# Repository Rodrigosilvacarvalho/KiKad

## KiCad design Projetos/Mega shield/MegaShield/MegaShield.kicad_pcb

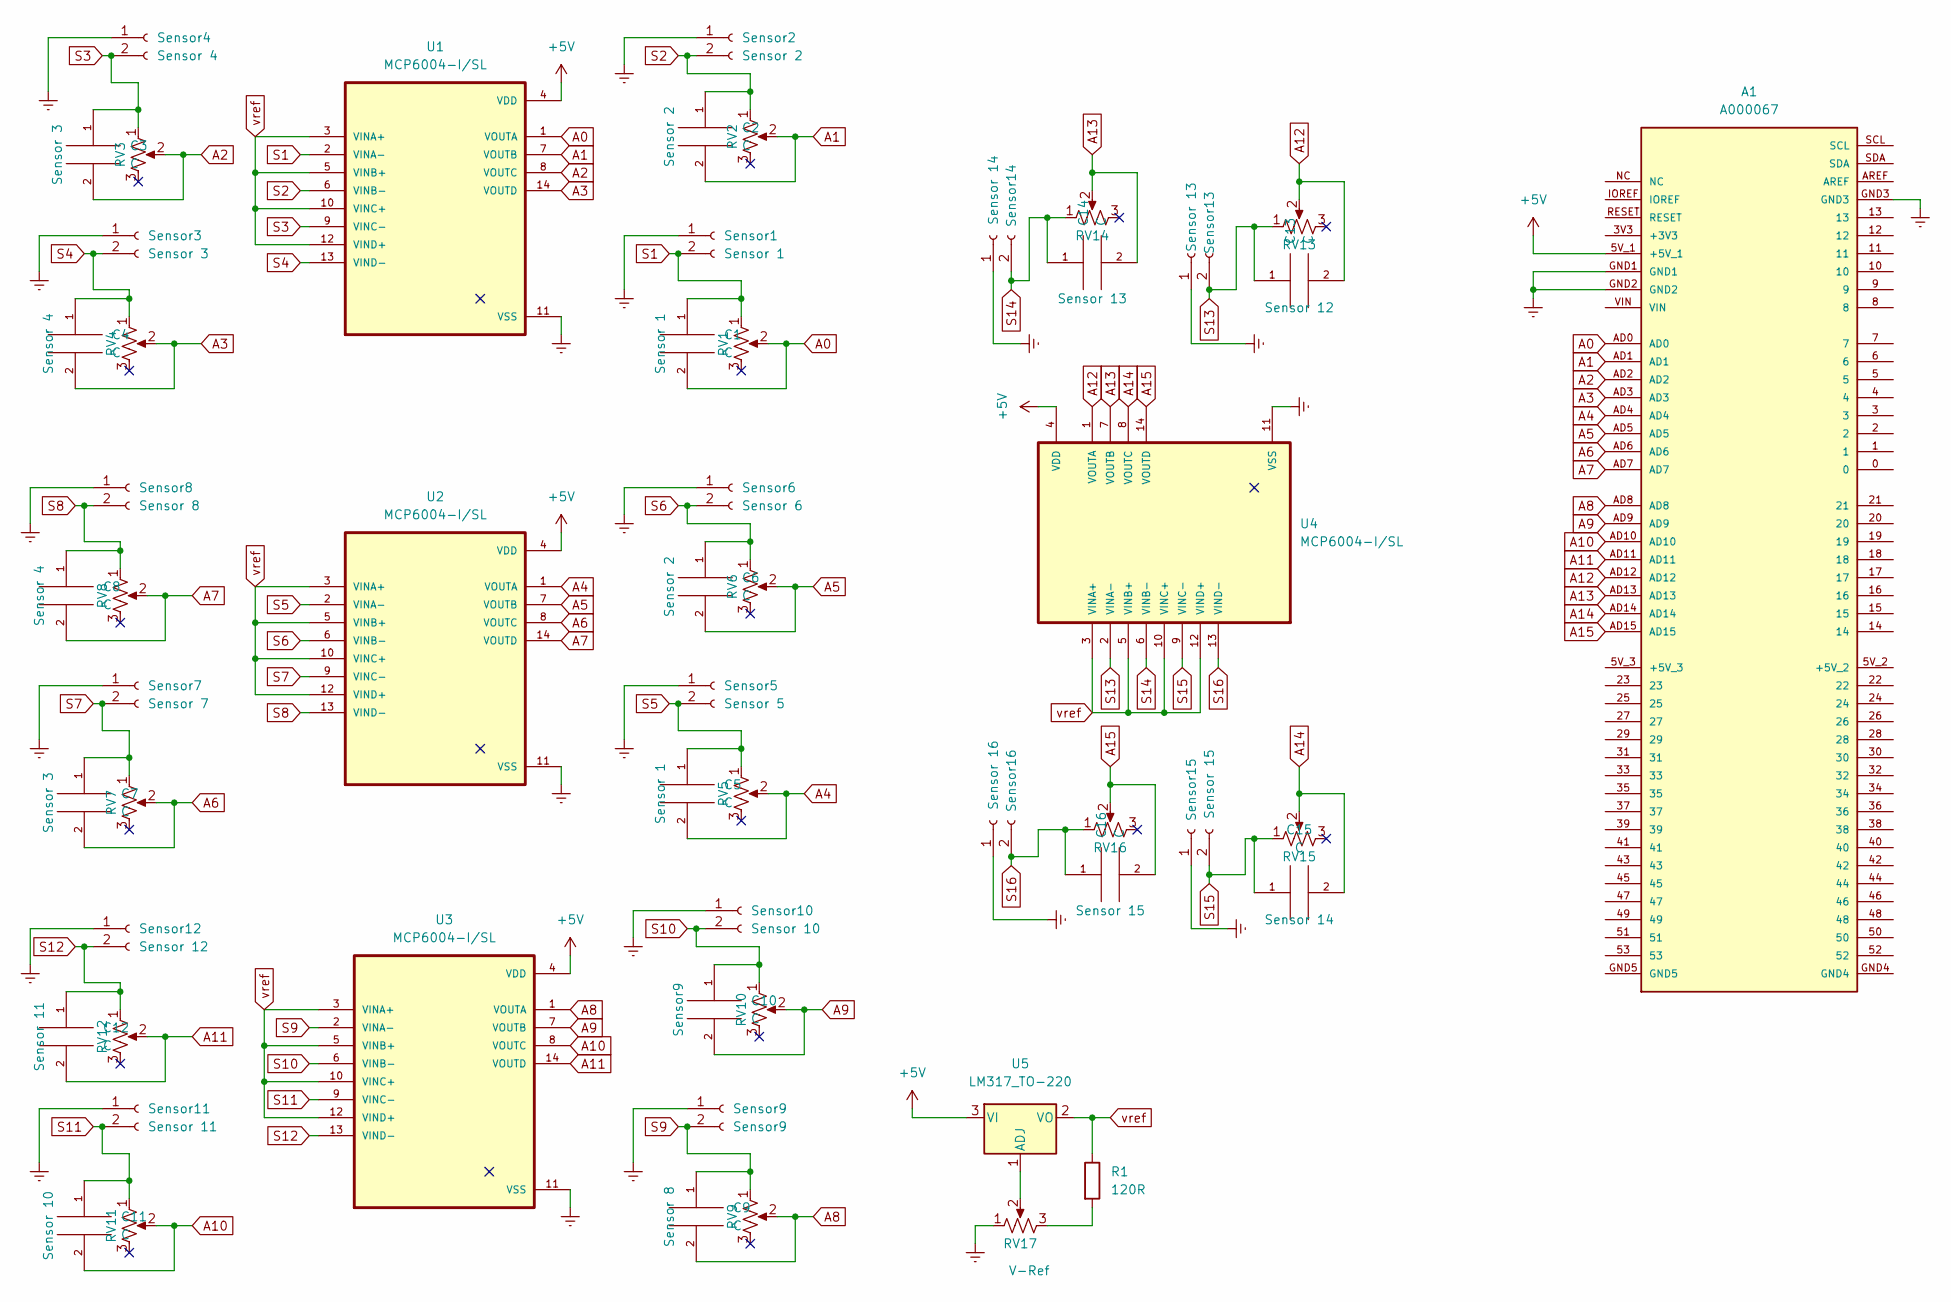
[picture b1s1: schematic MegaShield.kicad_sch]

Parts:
A1: A000067; ARDUINO_A000067
C1, C2, C3, C4, C5, C6, C7, C8, C9, C10, C11, C12, C13, C14, C15, C16: C; C_0805_2012Metric
R1: 120R; R_0805_2012Metric_Pad1.20x1.40mm_HandSolder
RV1, RV5: Sensor 1; Potentiometer_Bourns_3296W_Vertical
RV2, RV6: Sensor 2; Potentiometer_Bourns_3296W_Vertical
RV3, RV7: Sensor 3; Potentiometer_Bourns_3296W_Vertical
RV4, RV8: Sensor 4; Potentiometer_Bourns_3296W_Vertical
RV9: Sensor 8; Potentiometer_Bourns_3296W_Vertical
RV10: Sensor9; Potentiometer_Bourns_3296W_Vertical
RV11: Sensor 10; Potentiometer_Bourns_3296W_Vertical
RV12: Sensor 11; Potentiometer_Bourns_3296W_Vertical
RV13: Sensor 12; Potentiometer_Bourns_3296W_Vertical
RV14: Sensor 13; Potentiometer_Bourns_3296W_Vertical
RV15: Sensor 14; Potentiometer_Bourns_3296W_Vertical
RV16: Sensor 15; Potentiometer_Bourns_3296W_Vertical
RV17: V-Ref; Potentiometer_Bourns_3296W_Vertical
Sensor1: Sensor 1; JST_PH_B2B-PH-K_1x02_P2.00mm_Vertical
Sensor2: Sensor 2; JST_PH_B2B-PH-K_1x02_P2.00mm_Vertical
Sensor3: Sensor 3; JST_PH_B2B-PH-K_1x02_P2.00mm_Vertical
Sensor4: Sensor 4; JST_PH_B2B-PH-K_1x02_P2.00mm_Vertical
Sensor5: Sensor 5; JST_PH_B2B-PH-K_1x02_P2.00mm_Vertical
Sensor6: Sensor 6; JST_PH_B2B-PH-K_1x02_P2.00mm_Vertical
Sensor7: Sensor 7; JST_PH_B2B-PH-K_1x02_P2.00mm_Vertical
Sensor8: Sensor 8; JST_PH_B2B-PH-K_1x02_P2.00mm_Vertical
Sensor9: Sensor9; JST_PH_B2B-PH-K_1x02_P2.00mm_Vertical
Sensor10: Sensor 10; JST_PH_B2B-PH-K_1x02_P2.00mm_Vertical
Sensor11: Sensor 11; JST_PH_B2B-PH-K_1x02_P2.00mm_Vertical
Sensor12: Sensor 12; JST_PH_B2B-PH-K_1x02_P2.00mm_Vertical
Sensor13: Sensor 13; JST_PH_B2B-PH-K_1x02_P2.00mm_Vertical
Sensor14: Sensor 14; JST_PH_B2B-PH-K_1x02_P2.00mm_Vertical
Sensor15: Sensor 15; JST_PH_B2B-PH-K_1x02_P2.00mm_Vertical
Sensor16: Sensor 16; JST_PH_B2B-PH-K_1x02_P2.00mm_Vertical
U1, U2, U3, U4: MCP6004-I/SL; SOIC127P600X175-14N
U5: LM317_TO-220; TO-220-3_Vertical

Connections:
+5V: A1.5V_1 (+5V_1), U1.4 (VDD), U2.4 (VDD), U3.4 (VDD), U4.4 (VDD), U5.3 (VI)
A0: A1.AD0, C1.2, RV1.2, U1.1 (VOUTA)
A1: A1.AD1, C2.2, RV2.2, U1.7 (VOUTB)
A2: A1.AD2, C3.2, RV3.2, U1.8 (VOUTC)
A3: A1.AD3, C4.2, RV4.2, U1.14 (VOUTD)
A4: A1.AD4, C5.2, RV5.2, U2.1 (VOUTA)
A5: A1.AD5, C6.2, RV6.2, U2.7 (VOUTB)
A6: A1.AD6, C7.2, RV7.2, U2.8 (VOUTC)
A7: A1.AD7, C8.2, RV8.2, U2.14 (VOUTD)
A8: A1.AD8, C9.2, RV9.2, U3.1 (VOUTA)
A9: A1.AD9, C10.2, RV10.2, U3.7 (VOUTB)
A10: A1.AD10, C11.2, RV11.2, U3.8 (VOUTC)
A11: A1.AD11, C12.2, RV12.2, U3.14 (VOUTD)
A12: A1.AD12, C13.2, RV13.2, U4.1 (VOUTA)
A13: A1.AD13, C14.2, RV14.2, U4.7 (VOUTB)
A14: A1.AD14, C15.2, RV15.2, U4.8 (VOUTC)
A15: A1.AD15, C16.2, RV16.2, U4.14 (VOUTD)
Earth: A1.GND1, A1.GND2, A1.GND3, RV17.1, Sensor1.1, Sensor2.1, Sensor3.1, Sensor4.1, Sensor5.1, Sensor6.1, Sensor7.1, Sensor8.1, Sensor9.1, Sensor10.1, Sensor11.1, Sensor12.1, Sensor13.1, Sensor14.1, Sensor15.1, Sensor16.1, U1.11 (VSS), U2.11 (VSS), U3.11 (VSS), U4.11 (VSS)
unnamed: RV17.2, U5.1 (ADJ)
unnamed: R1.2, RV17.3
S1: C1.1, RV1.1, Sensor1.2, U1.2 (VINA-)
S2: C2.1, RV2.1, Sensor2.2, U1.6 (VINB-)
S3: C3.1, RV3.1, Sensor4.2, U1.9 (VINC-)
S4: C4.1, RV4.1, Sensor3.2, U1.13 (VIND-)
S5: C5.1, RV5.1, Sensor5.2, U2.2 (VINA-)
S6: C6.1, RV6.1, Sensor6.2, U2.6 (VINB-)
S7: C7.1, RV7.1, Sensor7.2, U2.9 (VINC-)
S8: C8.1, RV8.1, Sensor8.2, U2.13 (VIND-)
S9: C9.1, RV9.1, Sensor9.2, U3.2 (VINA-)
S10: C10.1, RV10.1, Sensor10.2, U3.6 (VINB-)
S11: C11.1, RV11.1, Sensor11.2, U3.9 (VINC-)
S12: C12.1, RV12.1, Sensor12.2, U3.13 (VIND-)
S13: C13.1, RV13.1, Sensor13.2, U4.2 (VINA-)
S14: C14.1, RV14.1, Sensor14.2, U4.6 (VINB-)
S15: C15.1, RV15.1, Sensor15.2, U4.9 (VINC-)
S16: C16.1, RV16.1, Sensor16.2, U4.13 (VIND-)
vref: R1.1, U1.3 (VINA+), U1.5 (VINB+), U1.10 (VINC+), U1.12 (VIND+), U2.3 (VINA+), U2.5 (VINB+), U2.10 (VINC+), U2.12 (VIND+), U3.3 (VINA+), U3.5 (VINB+), U3.10 (VINC+), U3.12 (VIND+), U4.3 (VINA+), U4.5 (VINB+), U4.10 (VINC+), U4.12 (VIND+), U5.2 (VO)

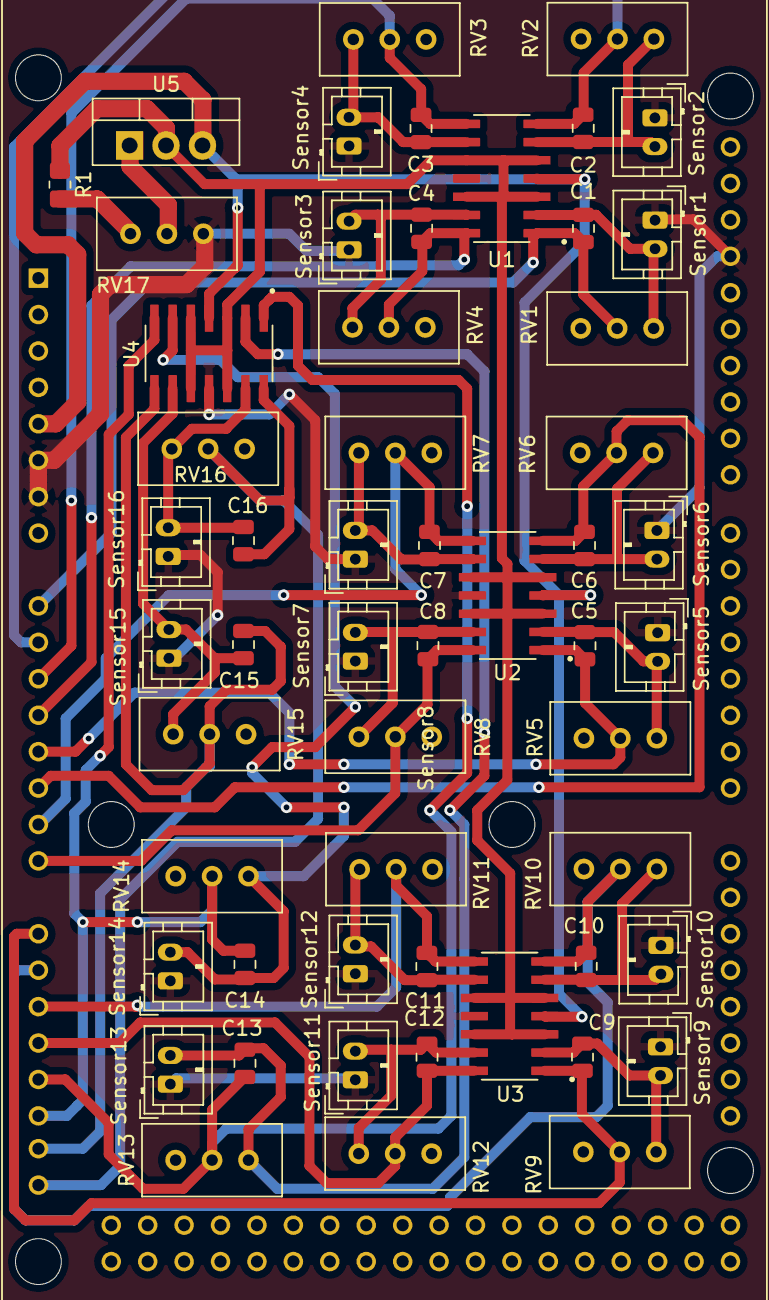
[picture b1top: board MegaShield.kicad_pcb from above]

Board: 2 copper layers, 56 parts (0 on the bottom side), 37 nets.

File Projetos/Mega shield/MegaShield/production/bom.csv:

Designator,Footprint,Quantity,Value,LCSC Part #
A1,ARDUINO_A000067,1,A000067,
U4,SOIC127P600X175-14N,1,MCP6004-I/SL,
U3,SOIC127P600X175-14N,1,MCP6004-I/SL,
U2,SOIC127P600X175-14N,1,MCP6004-I/SL,
U1,SOIC127P600X175-14N,1,MCP6004-I/SL,
C15,C_0805_2012Metric,1,C,
C16,C_0805_2012Metric,1,C,
C14,C_0805_2012Metric,1,C,
C13,C_0805_2012Metric,1,C,
Sensor14,JST_PH_B2B-PH-K_1x02_P2.00mm_Vertical,1,Sensor 14,
Sensor15,JST_PH_B2B-PH-K_1x02_P2.00mm_Vertical,1,Sensor 15,
Sensor13,JST_PH_B2B-PH-K_1x02_P2.00mm_Vertical,1,Sensor 13,
U5,TO-220-3_Vertical,1,LM317_TO-220,
RV13,Potentiometer_Bourns_3296W_Vertical,1,Sensor 12,
RV14,Potentiometer_Bourns_3296W_Vertical,1,Sensor 13,
RV15,Potentiometer_Bourns_3296W_Vertical,1,Sensor 14,
RV17,Potentiometer_Bourns_3296W_Vertical,1,V-Ref,
C10,C_0805_2012Metric,1,C,
C9,C_0805_2012Metric,1,C,
C11,C_0805_2012Metric,1,C,
C12,C_0805_2012Metric,1,C,
Sensor12,JST_PH_B2B-PH-K_1x02_P2.00mm_Vertical,1,Sensor 12,
Sensor10,JST_PH_B2B-PH-K_1x02_P2.00mm_Vertical,1,Sensor 10,
Sensor9,JST_PH_B2B-PH-K_1x02_P2.00mm_Vertical,1,Sensor9,
RV9,Potentiometer_Bourns_3296W_Vertical,1,Sensor 8,
RV10,Potentiometer_Bourns_3296W_Vertical,1,Sensor9,
RV11,Potentiometer_Bourns_3296W_Vertical,1,Sensor 10,
RV12,Potentiometer_Bourns_3296W_Vertical,1,Sensor 11,
C8,C_0805_2012Metric,1,C,
C7,C_0805_2012Metric,1,C,
C6,C_0805_2012Metric,1,C,
C5,C_0805_2012Metric,1,C,
Sensor8,JST_PH_B2B-PH-K_1x02_P2.00mm_Vertical,1,Sensor 8,
Sensor6,JST_PH_B2B-PH-K_1x02_P2.00mm_Vertical,1,Sensor 6,
Sensor5,JST_PH_B2B-PH-K_1x02_P2.00mm_Vertical,1,Sensor 5,
RV8,Potentiometer_Bourns_3296W_Vertical,1,Sensor 4,
RV7,Potentiometer_Bourns_3296W_Vertical,1,Sensor 3,
RV6,Potentiometer_Bourns_3296W_Vertical,1,Sensor 2,
RV5,Potentiometer_Bourns_3296W_Vertical,1,Sensor 1,
C2,C_0805_2012Metric,1,C,
RV3,Potentiometer_Bourns_3296W_Vertical,1,Sensor 3,
RV2,Potentiometer_Bourns_3296W_Vertical,1,Sensor 2,
RV1,Potentiometer_Bourns_3296W_Vertical,1,Sensor 1,
Sensor3,JST_PH_B2B-PH-K_1x02_P2.00mm_Vertical,1,Sensor 3,
Sensor2,JST_PH_B2B-PH-K_1x02_P2.00mm_Vertical,1,Sensor 2,
Sensor1,JST_PH_B2B-PH-K_1x02_P2.00mm_Vertical,1,Sensor 1,
RV16,Potentiometer_Bourns_3296W_Vertical,1,Sensor 15,
R1,R_0805_2012Metric_Pad1.20x1.40mm_HandSolder,1,120R,
C4,C_0805_2012Metric,1,C,
C1,C_0805_2012Metric,1,C,
C3,C_0805_2012Metric,1,C,
RV4,Potentiometer_Bourns_3296W_Vertical,1,Sensor 4,

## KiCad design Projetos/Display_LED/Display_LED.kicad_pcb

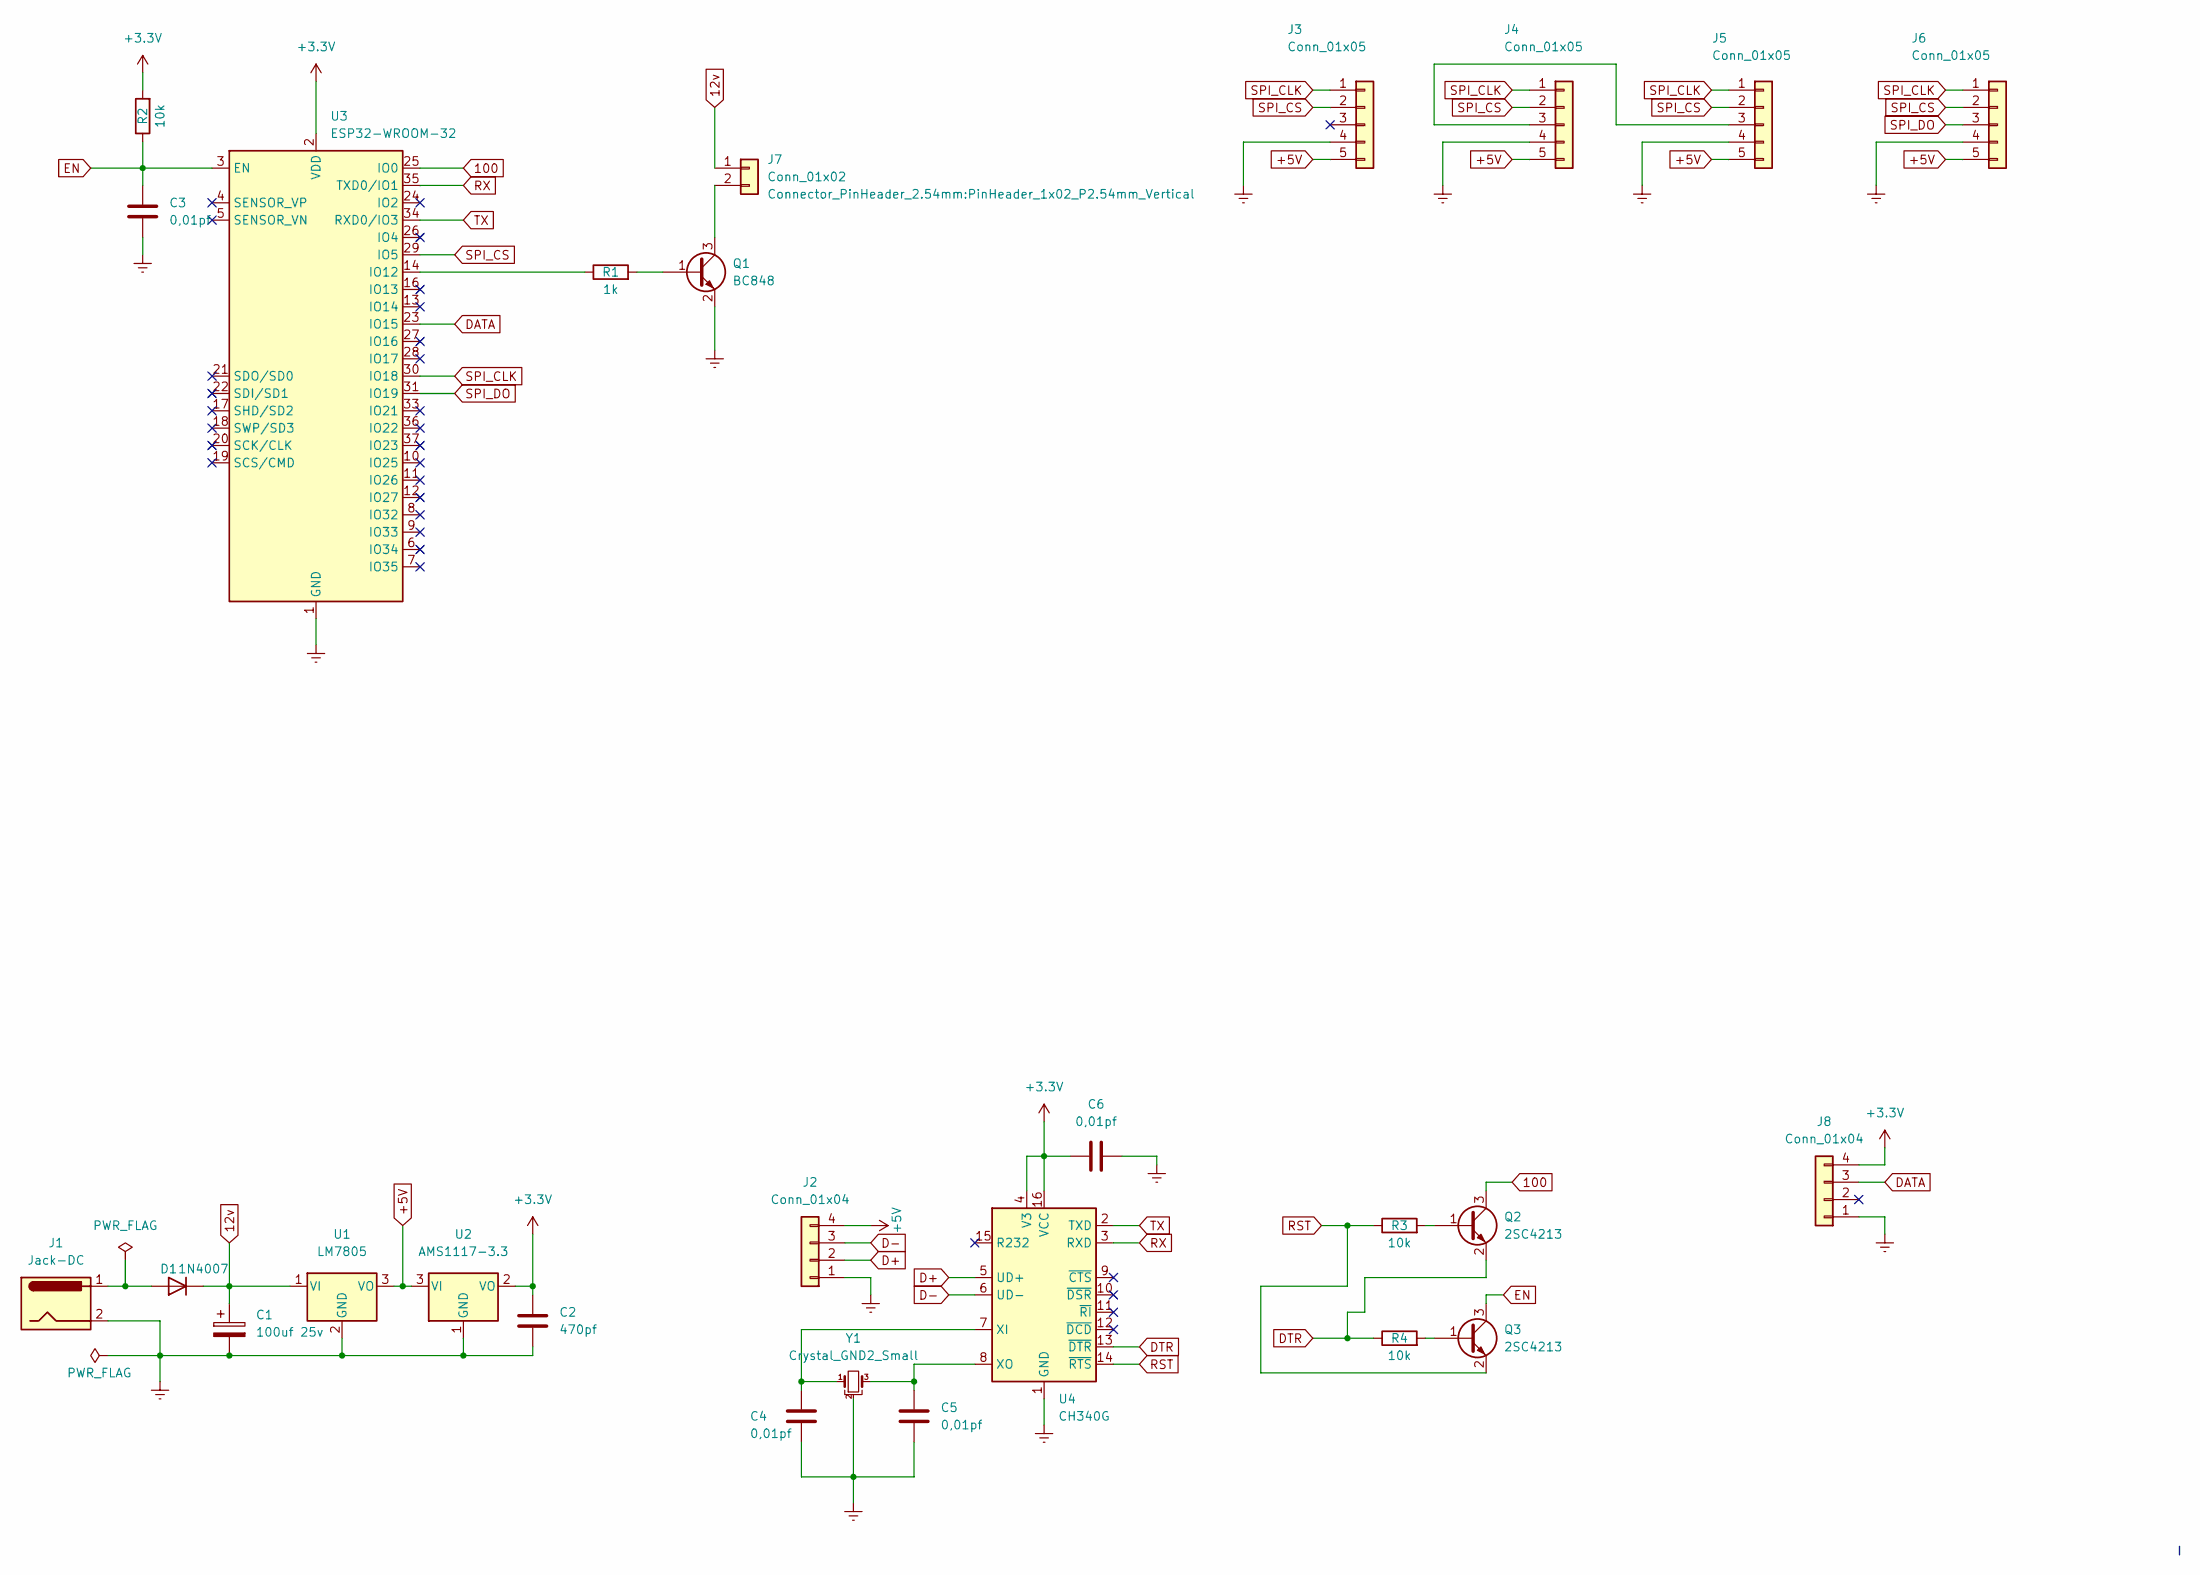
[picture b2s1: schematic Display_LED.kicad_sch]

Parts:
C1: 100uf 25v; CP_Elec_6.3x5.4
C2: 470pf; C_0805_2012Metric
C3, C4, C5, C6: 0,01pf; C_0805_2012Metric
D1: 1N4007; D_MicroMELF
J1: Jack-DC; BarrelJack_Horizontal
J2, J8: Conn_01x04; PinHeader_1x04_P2.54mm_Vertical
J3, J4, J5, J6: Conn_01x05; PinHeader_1x05_P2.54mm_Vertical
J7: Conn_01x02; PinHeader_1x02_P2.54mm_Vertical
Q1: BC848; SOT-23
Q2, Q3: 2SC4213; SOT-323_SC-70
R1: 1k; R_0805_2012Metric
R2, R3, R4: 10k; R_0805_2012Metric
U1: LM7805; SOT-223
U2: AMS1117-3.3; SOT-223-3_TabPin2
U3: ESP32-WROOM-32
U4: CH340G; SOIC-16_3.9x9.9mm_P1.27mm
Y1: Crystal_GND2_Small; Crystal_HC49-U-3Pin_Vertical

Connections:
12v: C1.1, D1.1 (K), J7.1, U1.1 (VI)
100: Q2.3 (C), U3.25 (IO0)
+3.3V: C2.1, C6.1, J8.4, R2.2, U2.2 (VO), U3.2 (VDD), U4.4 (V3), U4.16 (VCC)
+5V: J2.4, J3.5, J4.5, J5.5, J6.5, U1.3 (VO), U2.3 (VI)
D+: J2.2, U4.5 (UD+)
D-: J2.3, U4.6 (UD-)
DATA: J8.3, U3.23 (IO15)
DTR: Q2.2 (E), R4.1, U4.13 (~DTR)
EN: C3.1, Q3.3 (C), R2.1, U3.3 (EN)
unnamed: C4.1, U4.7 (XI), Y1.1
unnamed: C5.1, U4.8 (XO), Y1.3
unnamed: J4.3, J5.3
unnamed: J7.2, Q1.3 (C)
unnamed: Q1.1 (B), R1.2
unnamed: Q2.1 (B), R3.2
unnamed: Q3.1 (B), R4.2
unnamed: R1.1, U3.14 (IO12)
RST: Q3.2 (E), R3.1, U4.14 (~RTS)
RX: U3.35 (TXD0/IO1), U4.3 (RXD)
SPI_CLK: J3.1, J4.1, J5.1, J6.1, U3.30 (IO18)
SPI_CS: J3.2, J4.2, J5.2, J6.2, U3.29 (IO5)
SPI_DO: J6.3, U3.31 (IO19)
TX: U3.34 (RXD0/IO3), U4.2 (TXD)

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
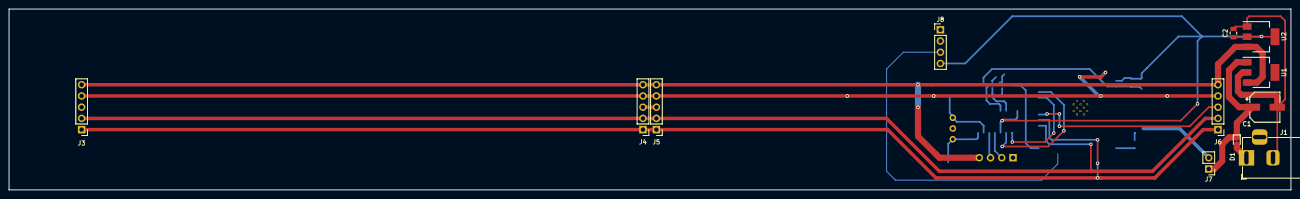
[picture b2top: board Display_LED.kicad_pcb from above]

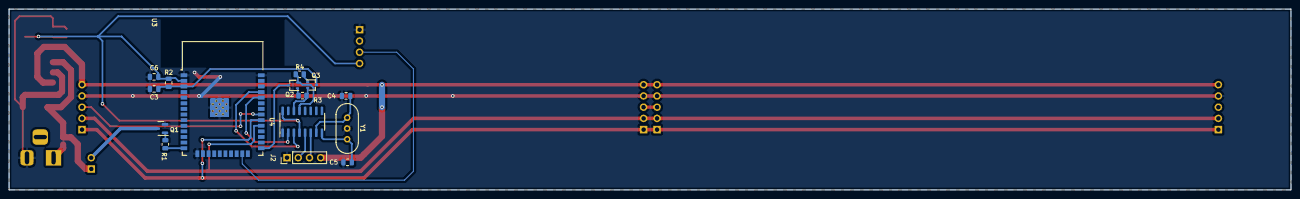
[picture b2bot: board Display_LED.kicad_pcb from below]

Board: 2 copper layers, 290.0 x 40.9 mm, 27 parts (15 on the bottom side), 25 nets.

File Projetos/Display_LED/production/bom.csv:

Designator,Footprint,Quantity,Value,LCSC Part #
U1,SOT-223,1,LM7805,
C2,C_0805_2012Metric,1,470pf,
C1,CP_Elec_6.3x5.4,1,100uf 25v,
U2,SOT-223-3_TabPin2,1,AMS1117-3.3,
J8,PinHeader_1x04_P2.54mm_Vertical,1,Conn_01x04,
J3,PinHeader_1x05_P2.54mm_Vertical,1,Conn_01x05,
J1,BarrelJack_Horizontal,1,Jack-DC,
J4,PinHeader_1x05_P2.54mm_Vertical,1,Conn_01x05,
J7,PinHeader_1x02_P2.54mm_Vertical,1,Conn_01x02,
J6,PinHeader_1x05_P2.54mm_Vertical,1,Conn_01x05,
J5,PinHeader_1x05_P2.54mm_Vertical,1,Conn_01x05,
D1,D_MicroMELF,1,1N4007,
R2,R_0805_2012Metric,1,10k,
C4,C_0805_2012Metric,1,"0,01pf",
Y1,Crystal_HC49-U-3Pin_Vertical,1,Crystal_GND2_Small,
J2,PinHeader_1x04_P2.54mm_Vertical,1,Conn_01x04,
C5,C_0805_2012Metric,1,"0,01pf",
Q1,SOT-23,1,BC848,
R3,R_0805_2012Metric,1,10k,
Q3,SOT-323_SC-70,1,2SC4213,
C6,C_0805_2012Metric,1,"0,01pf",
U4,SOIC-16_3.9x9.9mm_P1.27mm,1,CH340G,
U3,ESP32-WROOM-32,1,ESP32-WROOM-32,
R4,R_0805_2012Metric,1,10k,
C3,C_0805_2012Metric,1,"0,01pf",
Q2,SOT-323_SC-70,1,2SC4213,
R1,R_0805_2012Metric,1,1k,

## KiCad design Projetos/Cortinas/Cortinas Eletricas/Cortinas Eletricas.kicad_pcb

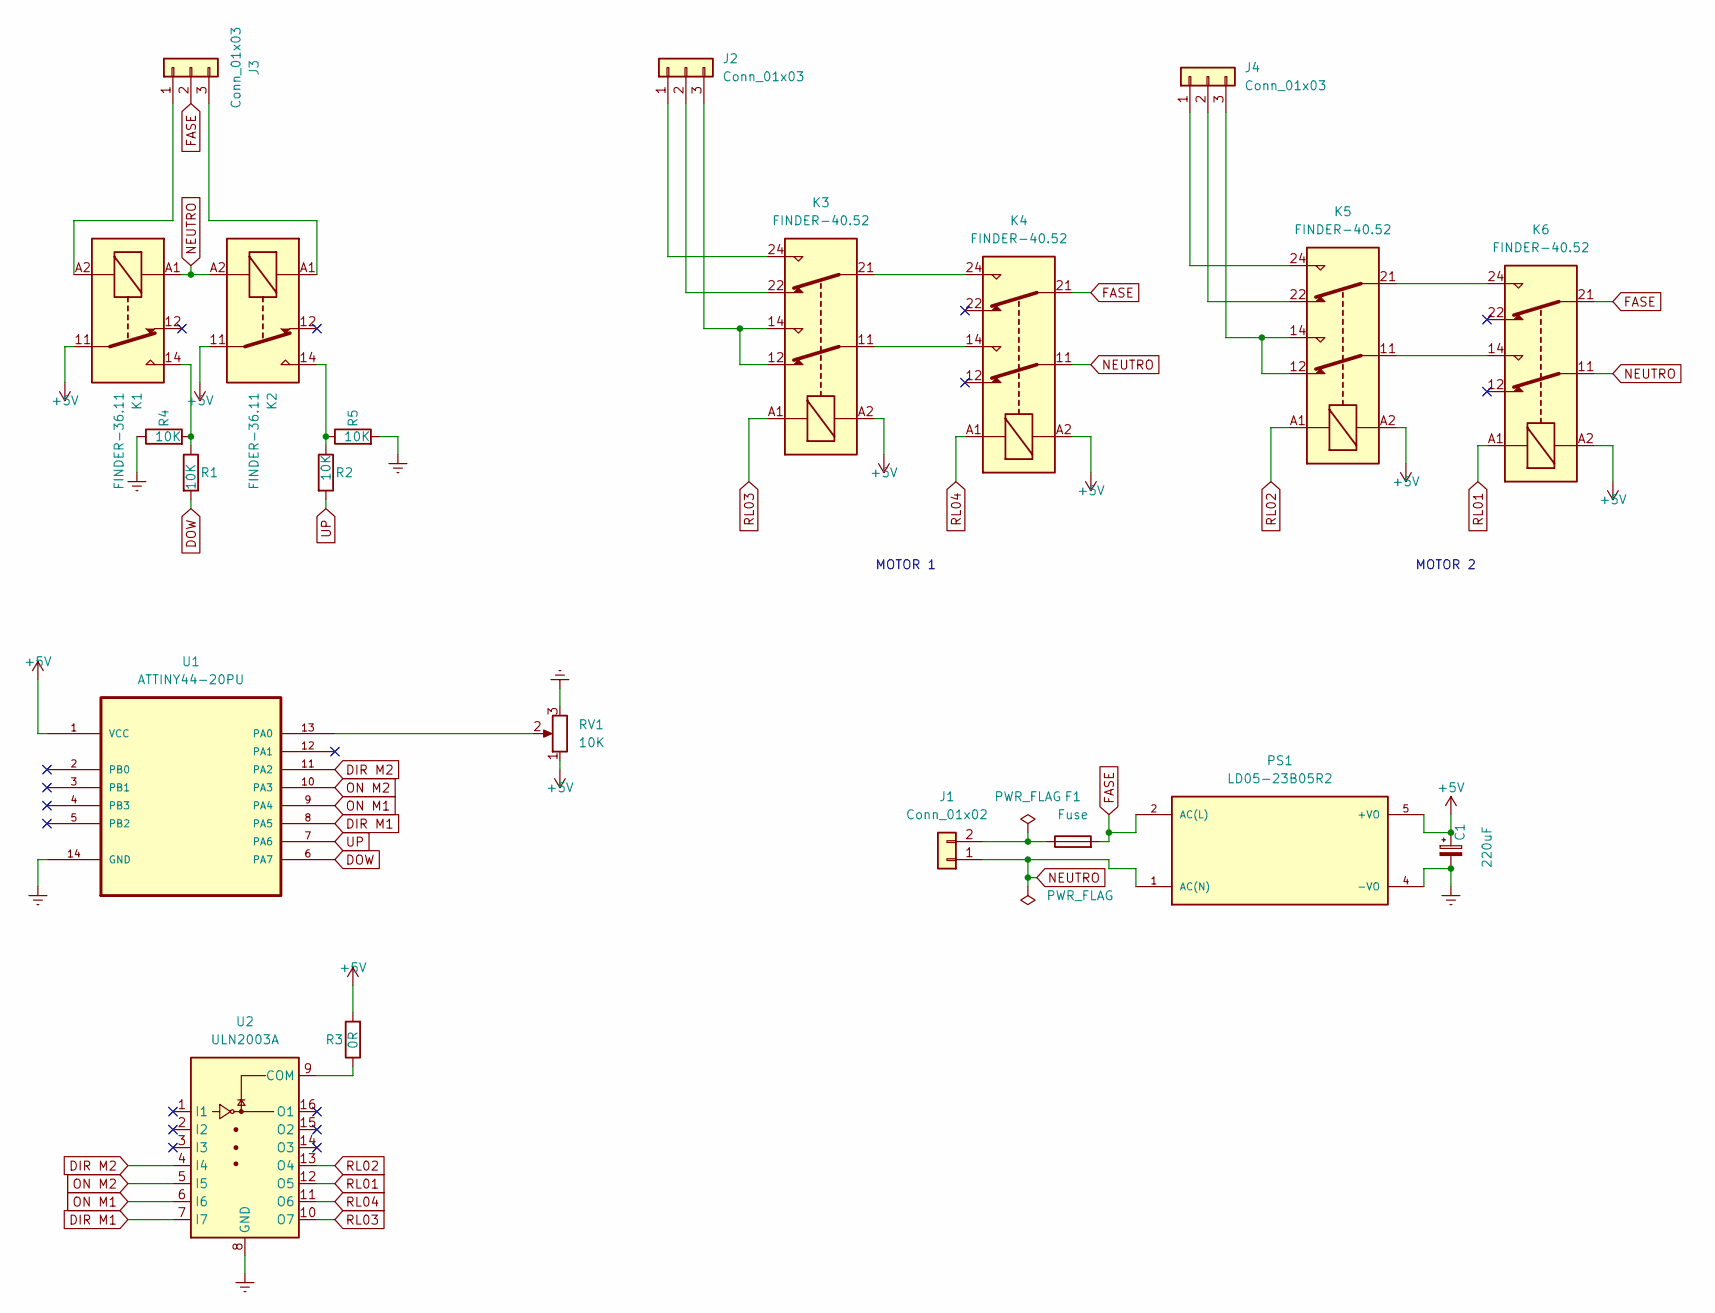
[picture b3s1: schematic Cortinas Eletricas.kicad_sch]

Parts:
C1: 220uF; CP_Radial_D8.0mm_P2.50mm
F1: Fuse; Fuse_Bourns_MF-RHT070
J1: Conn_01x02; TerminalBlock_Phoenix_MKDS-1,5-2_1x02_P5.00mm_Horizontal
J2, J3, J4: Conn_01x03; TerminalBlock_Phoenix_MKDS-1,5-3_1x03_P5.00mm_Horizontal
K1, K2: FINDER-36.11; Relay_SPDT_Finder_40.31
K3, K4, K5, K6: FINDER-40.52; Relay_DPDT_Finder_40.52
PS1: LD05-23B05R2; CONV_LD05-23B05R2; PARTREV 2020.06.30-A/2
R1, R2, R4, R5: 10K; R_Axial_DIN0204_L3.6mm_D1.6mm_P5.08mm_Horizontal
R3: 0R; R_Axial_DIN0204_L3.6mm_D1.6mm_P5.08mm_Horizontal
RV1: 10K; Potentiometer_Bourns_3296W_Vertical
U1: ATTINY44-20PU; DIP-14_W10.16mm_LongPads; MPN ATTINY44-20PU
U2: ULN2003A; DIP-16_W10.16mm_LongPads

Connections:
DIR M1: U1.10 (PA3), U2.5 (I5)
DIR M2: U1.11 (PA2), U2.4 (I4)
DOW: R1.2, U1.6 (PA7)
FASE: F1.2, J3.2, K4.21, K6.21, PS1.2 (AC(L))
NEUTRO: J1.1, K1.A1, K2.A2, K4.11, K6.11, PS1.1 (AC(N))
unnamed: F1.1, J1.2
unnamed: J4.3, K5.12, K5.14
unnamed: K1.14, R1.1, R4.2
unnamed: J3.1, K1.A2
unnamed: K2.14, R2.1, R5.1
unnamed: J3.3, K2.A1
unnamed: K3.11, K4.14
unnamed: J2.3, K3.12, K3.14
unnamed: K3.21, K4.24
unnamed: J2.2, K3.22
unnamed: J2.1, K3.24
unnamed: K5.11, K6.14
unnamed: K5.21, K6.24
unnamed: J4.2, K5.22
unnamed: J4.1, K5.24
unnamed: RV1.2, U1.13 (PA0)
unnamed: R3.1, U2.9 (COM)
ON M1: U1.8 (PA5), U2.7 (I7)
ON M2: U1.9 (PA4), U2.6 (I6)
RL01: K6.A1, U2.12 (O5)
RL02: K5.A1, U2.13 (O4)
RL03: K3.A1, U2.10 (O7)
RL04: K4.A1, U2.11 (O6)
RST: U1.4 (PB3)
UP: R2.2, U1.7 (PA6)

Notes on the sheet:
MOTOR 2
MOTOR 1

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
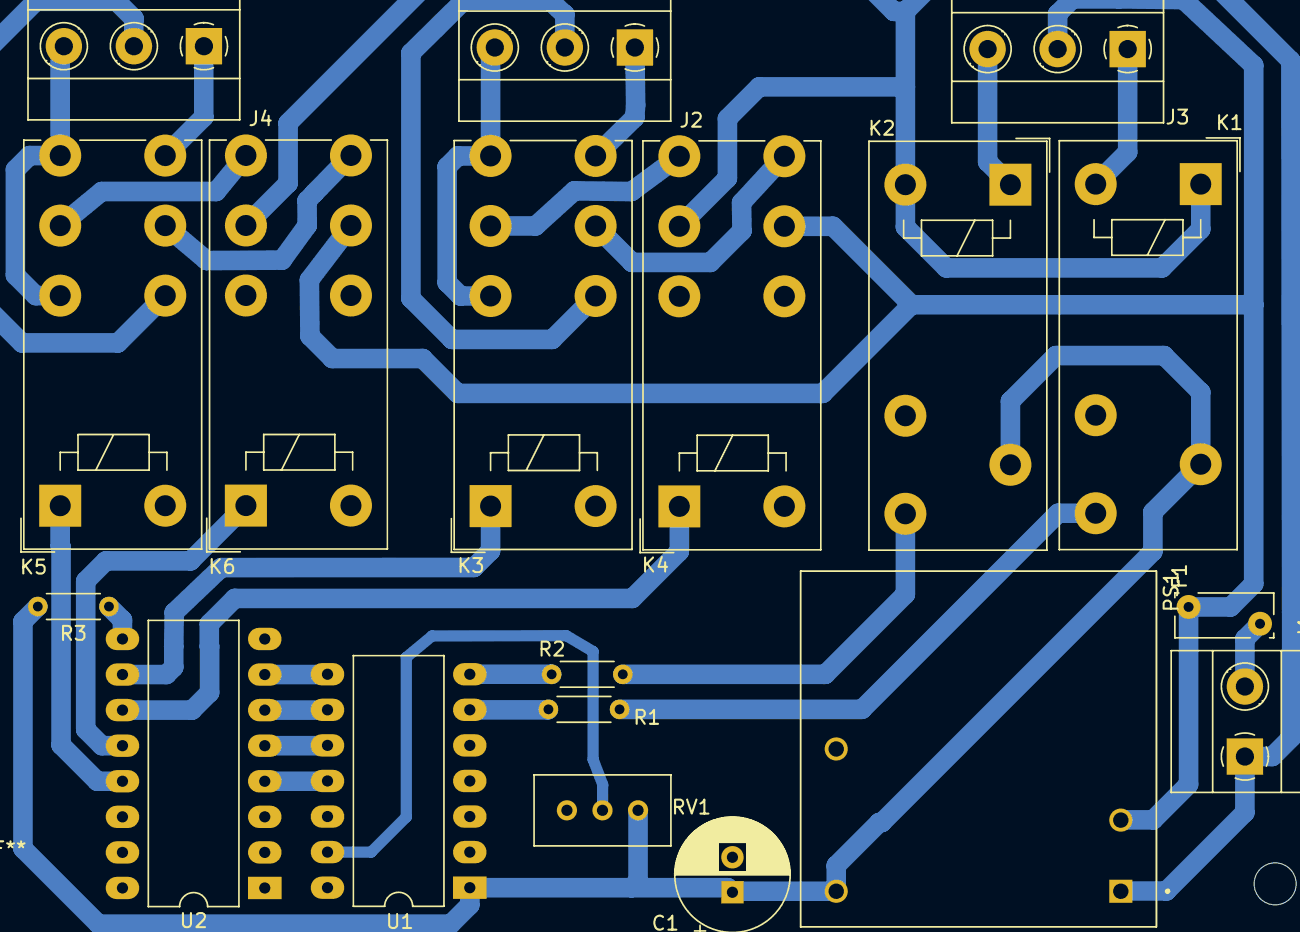
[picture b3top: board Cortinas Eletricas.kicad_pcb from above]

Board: 2 copper layers, 19 parts (0 on the bottom side), 31 nets.

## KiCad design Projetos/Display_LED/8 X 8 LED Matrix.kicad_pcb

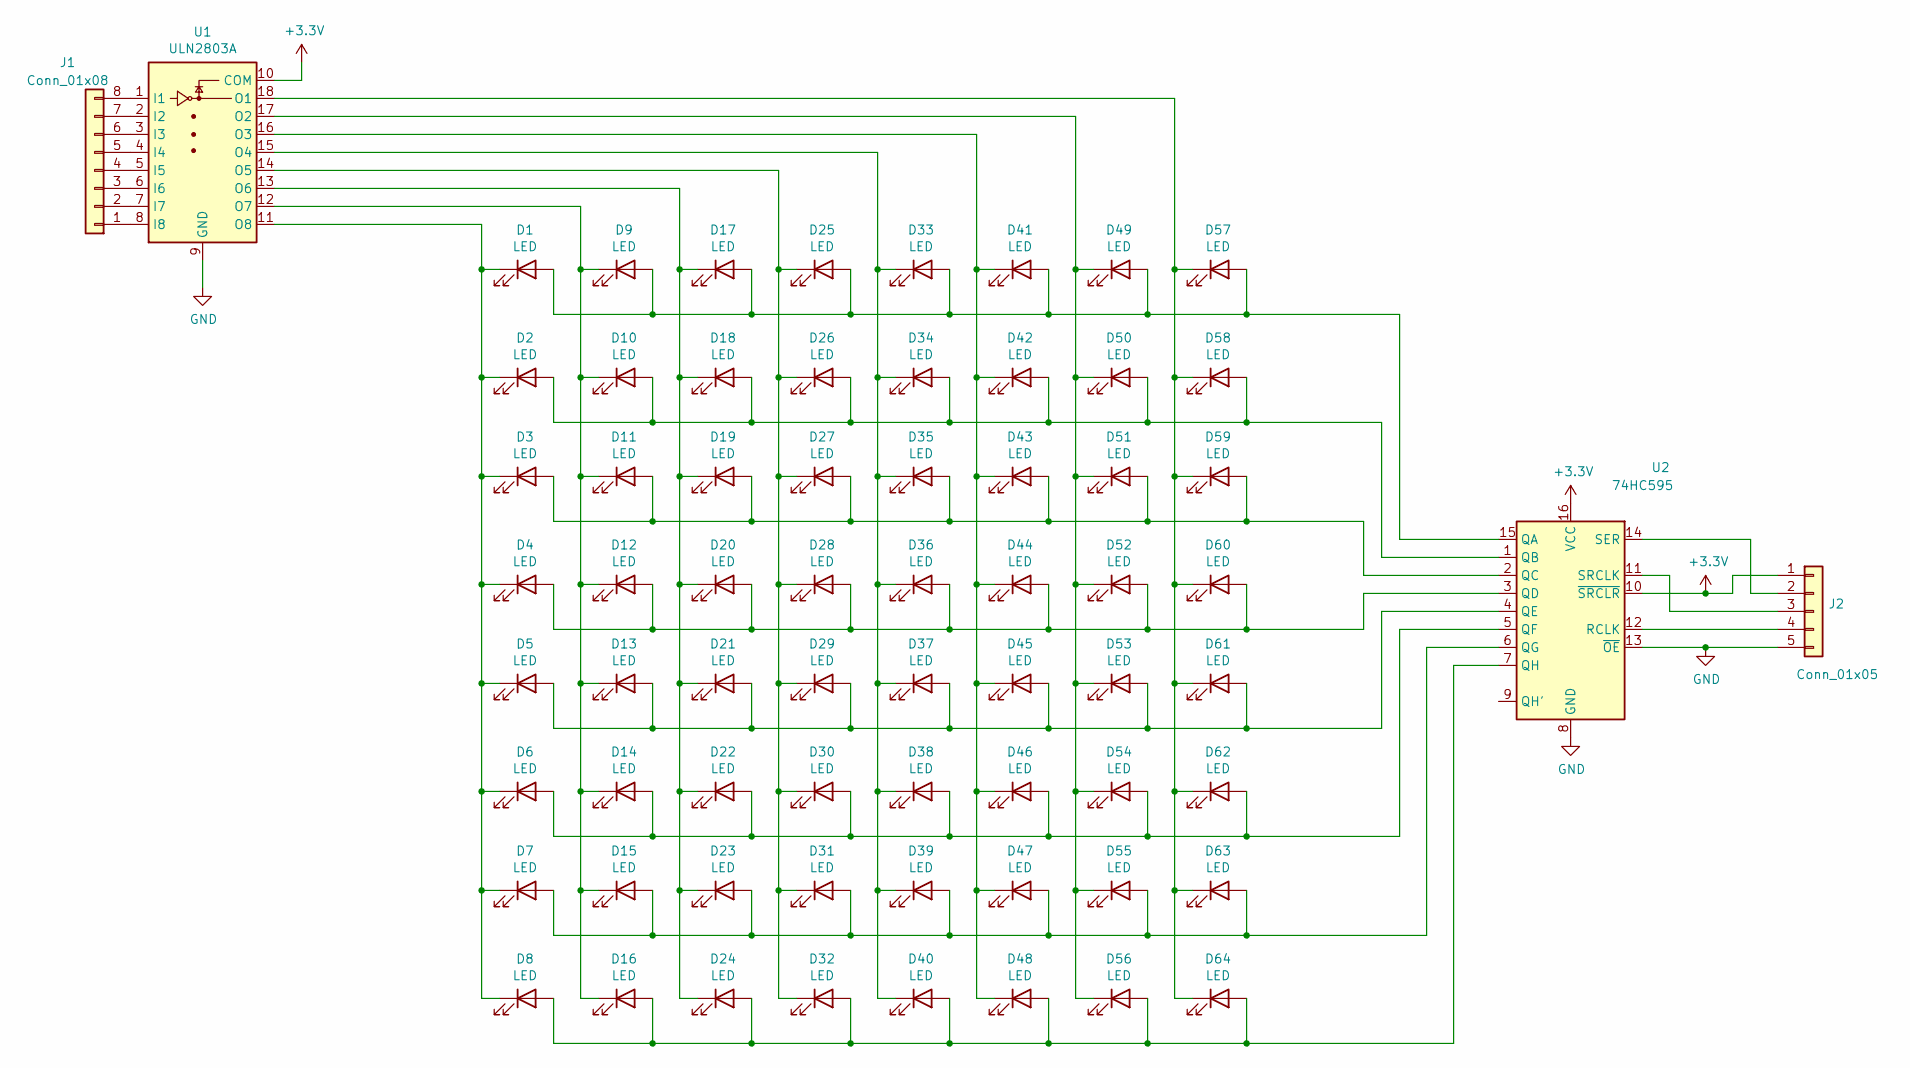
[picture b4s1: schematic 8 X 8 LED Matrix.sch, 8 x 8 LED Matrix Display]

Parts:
D1, D2, D3, D4, D5, D6, D7, D8, D9, D10, D11, D12, D13, D14, D15, D16, D17, D18, D19, D20, D21, D22, D23, D24, D25, D26, D27, D28, D29, D30, D31, D32, D33, D34, D35, D36, D37, D38, D39, D40, D41, D42, D43, D44, D45, D46, D47, D48, D49, D50, D51, D52, D53, D54, D55, D56, D57, D58, D59, D60, D61, D62, D63, D64: LED; LED_0603_1608Metric
J1: Conn_01x08; PinHeader_1x08_P2.54mm_Vertical_SMD_Pin1Left
J2: Conn_01x05; PinHeader_1x05_P2.54mm_Vertical_SMD_Pin1Left
U1: ULN2803A; DIP-18_W7.62mm_SMDSocket_SmallPads
U2: 74HC595; DIP-16_W7.62mm_SMDSocket_SmallPads

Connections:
+3V3: J2.1, U1.10 (COM), U2.10 (~SRCLR), U2.16 (VCC)
GND: J2.5, U1.9 (GND), U2.8 (GND), U2.13 (~OE)
unnamed: D1.1 (K), D2.1 (K), D3.1 (K), D4.1 (K), D5.1 (K), D6.1 (K), D7.1 (K), D8.1 (K), U1.11 (O8)
unnamed: D1.2 (A), D9.2 (A), D17.2 (A), D25.2 (A), D33.2 (A), D41.2 (A), D49.2 (A), D57.2 (A), U2.15 (QA)
unnamed: D9.1 (K), D10.1 (K), D11.1 (K), D12.1 (K), D13.1 (K), D14.1 (K), D15.1 (K), D16.1 (K), U1.12 (O7)
unnamed: D2.2 (A), D10.2 (A), D18.2 (A), D26.2 (A), D34.2 (A), D42.2 (A), D50.2 (A), D58.2 (A), U2.1 (QB)
unnamed: D3.2 (A), D11.2 (A), D19.2 (A), D27.2 (A), D35.2 (A), D43.2 (A), D51.2 (A), D59.2 (A), U2.2 (QC)
unnamed: D4.2 (A), D12.2 (A), D20.2 (A), D28.2 (A), D36.2 (A), D44.2 (A), D52.2 (A), D60.2 (A), U2.3 (QD)
unnamed: D5.2 (A), D13.2 (A), D21.2 (A), D29.2 (A), D37.2 (A), D45.2 (A), D53.2 (A), D61.2 (A), U2.4 (QE)
unnamed: D6.2 (A), D14.2 (A), D22.2 (A), D30.2 (A), D38.2 (A), D46.2 (A), D54.2 (A), D62.2 (A), U2.5 (QF)
unnamed: D7.2 (A), D15.2 (A), D23.2 (A), D31.2 (A), D39.2 (A), D47.2 (A), D55.2 (A), D63.2 (A), U2.6 (QG)
unnamed: D8.2 (A), D16.2 (A), D24.2 (A), D32.2 (A), D40.2 (A), D48.2 (A), D56.2 (A), D64.2 (A), U2.7 (QH)
unnamed: D17.1 (K), D18.1 (K), D19.1 (K), D20.1 (K), D21.1 (K), D22.1 (K), D23.1 (K), D24.1 (K), U1.13 (O6)
unnamed: D25.1 (K), D26.1 (K), D27.1 (K), D28.1 (K), D29.1 (K), D30.1 (K), D31.1 (K), D32.1 (K), U1.14 (O5)
unnamed: D33.1 (K), D34.1 (K), D35.1 (K), D36.1 (K), D37.1 (K), D38.1 (K), D39.1 (K), D40.1 (K), U1.15 (O4)
unnamed: D41.1 (K), D42.1 (K), D43.1 (K), D44.1 (K), D45.1 (K), D46.1 (K), D47.1 (K), D48.1 (K), U1.16 (O3)
unnamed: D49.1 (K), D50.1 (K), D51.1 (K), D52.1 (K), D53.1 (K), D54.1 (K), D55.1 (K), D56.1 (K), U1.17 (O2)
unnamed: D57.1 (K), D58.1 (K), D59.1 (K), D60.1 (K), D61.1 (K), D62.1 (K), D63.1 (K), D64.1 (K), U1.18 (O1)
unnamed: J1.1, U1.8 (I8)
unnamed: J1.2, U1.7 (I7)
unnamed: J1.3, U1.6 (I6)
unnamed: J1.4, U1.5 (I5)
unnamed: J1.5, U1.4 (I4)
unnamed: J1.6, U1.3 (I3)
unnamed: J1.7, U1.2 (I2)
unnamed: J1.8, U1.1 (I1)
unnamed: J2.2, U2.14 (SER)
unnamed: J2.3, U2.11 (SRCLK)
unnamed: J2.4, U2.12 (RCLK)

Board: 2 copper layers, 68 parts (0 on the bottom side), 29 nets, no tracks yet.

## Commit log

2023-03-11 UP
    Atualizaçao
